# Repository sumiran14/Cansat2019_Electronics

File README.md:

# Cansat2019_Electronics
@Shikhar1998
Shikhar1998 GPS Code Update  …
I didn't have had the hardware to verify the code, just a basic GPS logic, I hope this will ease some of your work. Rest, a nice work done by you guys.

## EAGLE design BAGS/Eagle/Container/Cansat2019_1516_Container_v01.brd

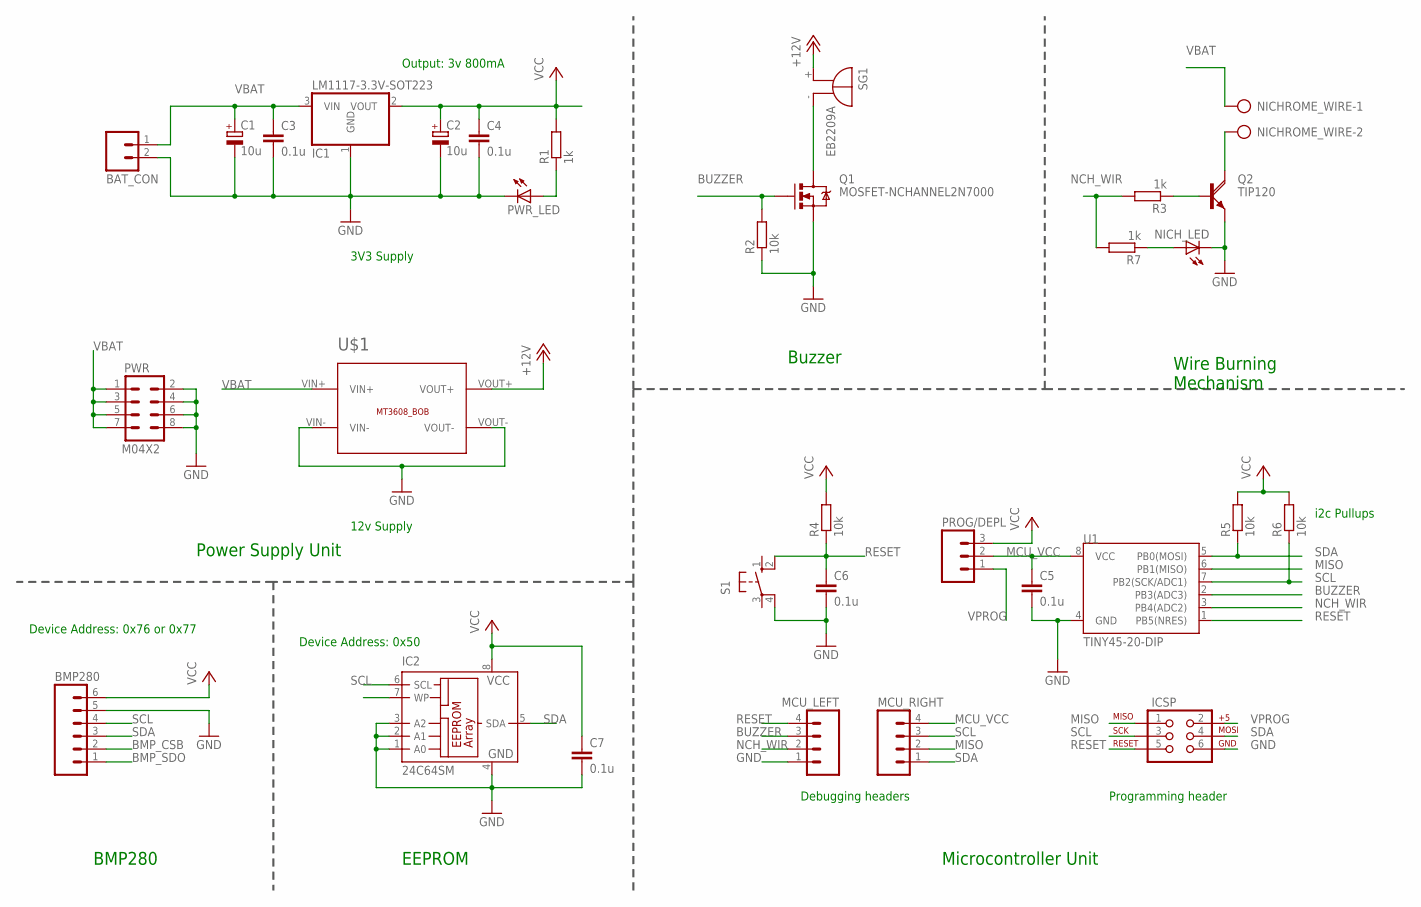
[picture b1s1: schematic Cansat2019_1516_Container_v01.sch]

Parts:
BAT_CON: M02; 02P
BMP280: M06; 06P
C1, C2: 10u; E2,5-6
C3, C4, C5, C6, C7: 0.1u; C025-025X050
IC1: LM1117-3.3V-SOT223; SOT223
IC2: 24C64SM; SO-08M
ICSP: AVR_SPI_PRG_6NS; 2X3-NS
MCU_LEFT: M04; 04P
MCU_RIGHT: M04; 04P
NICHROME_WIRE: AK500/2-H
NICH_LED: LED3MM
PROG/DEPL: M03PTH; 1X03
PWR: M04X2; 2X4
PWR_LED: LED3MM
Q1: MOSFET-NCHANNEL2N7000; TO-92
Q2: TIP120; TO220AH
R1, R3, R7: 1k; 0204/7
R2, R4, R5, R6: 10k; 0204/7
S1: PUSH-BUTTON-6MM; B3F-10XX
SG1: EB2209A
U1: TINY45-20-DIP; DIP08
U$1: MT3608_BOB

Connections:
+12V: SG1.+, U$1.VOUT+; also elsewhere on the board
BMP_CSB: BMP280.2
BMP_SDO: BMP280.1
BUZZER: MCU_LEFT.3, Q1.2 (G), R2.2, U1.2 (PB3(ADC3))
GND: BAT_CON.2, BMP280.5, C1.-, C2.-, C3.2, C4.2, C5.2, C6.2, C7.2, IC1.1 (GND), IC2.1 (A0), IC2.2 (A1), IC2.3 (A2), IC2.4 (GND), ICSP.6, MCU_LEFT.1, NICH_LED.K (C), PWR.2, PWR.4, PWR.6, PWR.8, PWR_LED.K (C), Q1.1 (S), Q2.E, R2.1, S1.4 (P1), U1.4 (GND), U$1.VIN-, U$1.VOUT-; also elsewhere on the board
MCU_VCC: C5.1, MCU_RIGHT.4, PROG/DEPL.2, U1.8 (VCC)
MISO: ICSP.1, MCU_RIGHT.2, U1.6 (PB1(MISO))
unnamed: Q1.3 (D), SG1.-
unnamed: NICHROME_WIRE.2, Q2.C
unnamed: PWR_LED.A, R1.1
unnamed: Q2.B, R3.1
unnamed: NICH_LED.A, R7.1
NCH_WIR: MCU_LEFT.2, R3.2, R7.2, U1.3 (PB4(ADC2))
RESET: C6.1, ICSP.5, MCU_LEFT.4, R4.1, S1.2 (S1), U1.1 (PB5(NRES))
SCL: BMP280.4, IC2.6 (SCL), ICSP.3, MCU_RIGHT.3, R6.1, U1.7 (PB2(SCK/ADC1))
SDA: BMP280.3, IC2.5 (SDA), ICSP.4, MCU_RIGHT.1, R5.1, U1.5 (PB0(MOSI))
VCC: BMP280.6, C2.+, C4.1, C7.1, IC1.2 (VOUT), IC2.8 (VCC), PROG/DEPL.3, R1.2, R4.2, R5.2, R6.2
VPROG: ICSP.2, PROG/DEPL.1

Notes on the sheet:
Power Supply Unit
Buzzer
Wire Burning Mechanism
Debugging headers
Programming header
Microcontroller Unit
3V3 Supply
12v Supply
BMP280
i2c Pullups
Output: 3v 800mA
Device Address: 0x50
EEPROM
Device Address: 0x76 or 0x77

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
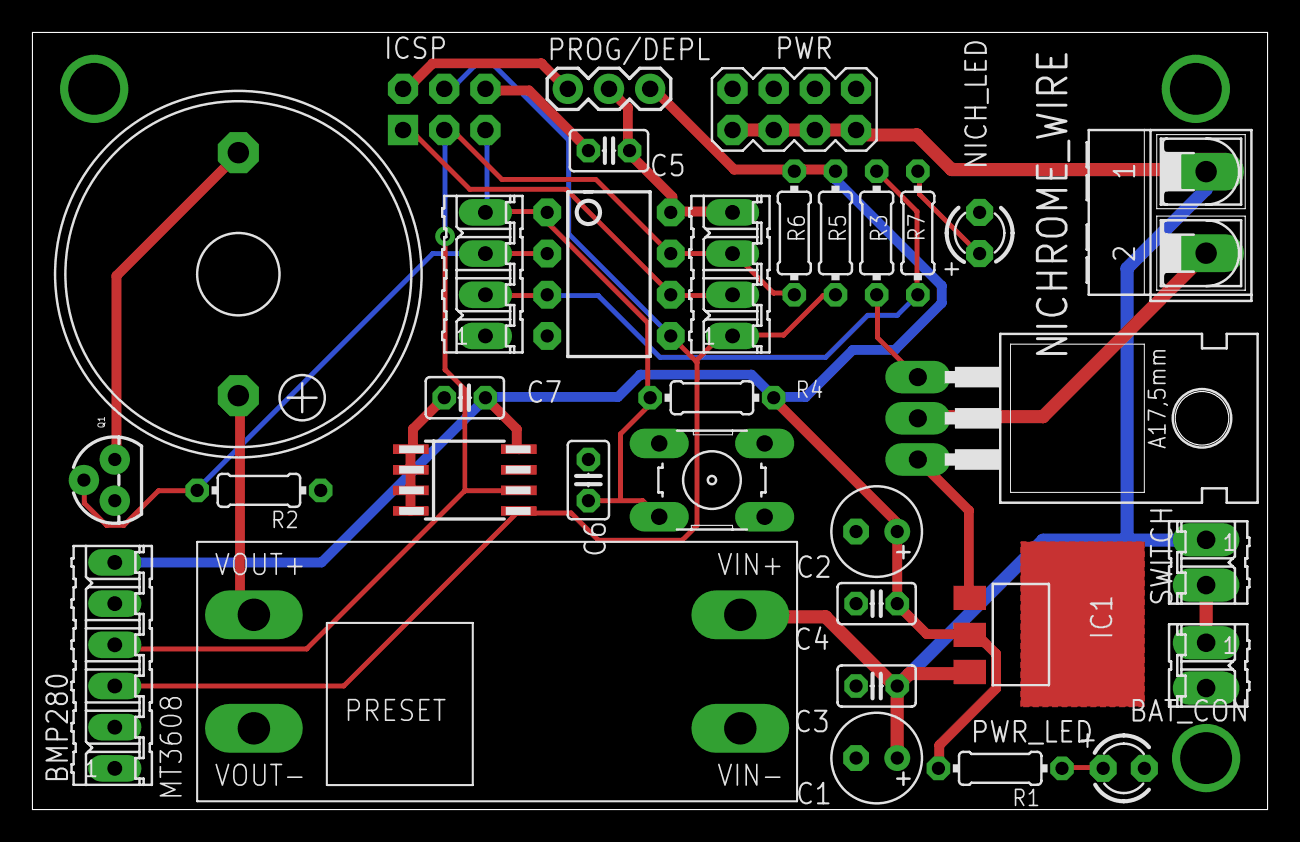
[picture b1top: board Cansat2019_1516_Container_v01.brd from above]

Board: 2 copper layers, 76.2 x 47.9 mm, 33 parts (0 on the bottom side), 18 nets.

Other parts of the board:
MT3608: MT3608_BOB
SWITCH: 02P

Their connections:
+12V: MT3608.VOUT+; also elsewhere on the board
GND: MT3608.VIN-, MT3608.VOUT-; also elsewhere on the board

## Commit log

2018-12-19 Initail Commit: Basic code tested on 18/12/2018
2018-12-19 This code finds the RPM
2018-12-19 This code finds RPM: Added few more comments
2018-12-19 Changed the code logic after discussion
2018-12-29 adding the first Draft of many sensor's code
2018-12-29 GPS Code Update
    I didn't have had the hardware to verify the code, just a basic GPS logic, I hope this will ease some of your work. Rest, a nice work done by you guys.
2018-12-30 Adding gps_altitude field in class packet
2018-12-30 Changed gps_time datatype to volatile int32_t
2018-12-30 Minor changes in GPS: assign packet variables values read by GPS
2018-12-30 Added Battery Voltage reader functions
2018-12-31 trial
2019-01-03 Intro
2019-01-03 Create Intro
2019-01-03 get Mission time using RTC from SAMD using Wire1
2019-01-03 Wire1 Code for getting gyroscope and accelerometer readings
    function for Integrating these readings to get pitch and roll is left
2019-01-04 Changing it to be SAMD Wire1 compatible
2019-01-04 Added comments and to be used at address 0x69
2019-01-04 Battery voltage - SAMD by @marvellouslad-9
2019-01-04 Update SDCard.ino
    Added #ifndefs for toggling serial output
2019-01-05 Now its working with SAMD: TESTED OK
2019-01-06 code to be compiled and uploaded to samd
    3/8 features integrated.
2019-01-06 Changing multiplying factors to make it less sensitive to vibrations
2019-01-06 Update packet.h
    Changed the UTC format before. I am still not sure if it is correct yet.
2019-01-06 Add files via upload
    Added SD card functionality.
    The mission timestamp needs to be updated with the RTC time stamp.
2019-01-06 Integrated Packet functionality
    packet class has also changed slightly. There is no more need to maintain the packet code in other folders.
    Same goes for battery voltage, sd card and sercom
2019-01-06 Integrated Sanuj's RTC code
2019-01-07 Deleted redundant files
2019-01-07 Added xbee file to cansat_prototype_1
2019-01-08 minor change in xbee code
2019-01-10 Camera buttonpressCamButton function
2019-01-19 ADDING TEENSY PROTOTYPE
2019-01-19 BMP RTC MPU Working together with I2C bus
2019-01-19 Added xbee code
2019-01-19 Added SPI SDCard
2019-01-19 Added VOLTAGE and PacketCOUNT
2019-01-19 Added HALL SENSOR CODE
2019-02-03 Create in
2019-02-03 NRF24l01 - Tested
2019-02-06 Delete bosch-bmp280.lbr
    The library is of IC. We are looking for breakout board.
2019-02-09 MPU9250 Tested with Arduino Pro-mini
2019-03-03 Code for Hall seperately tested. INTEGRATED CODE IS YET TO BE TESTED
2019-03-06 XBEE Interrupts Working
2019-03-06 Deleting Wrong folder of TEENSY

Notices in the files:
parts and their libraries:
SparkFun-Connectors: Licensing: Creative Commons ShareAlike 4.0 International - https://creativecommons.org/licenses/by-sa/4.0
